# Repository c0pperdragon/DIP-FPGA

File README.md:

# DIP-FPGA
Breakout boards for FPGAs in DIP format.

## MachXO2 in a DIP 20
Assembled boards can be bought from
[my store at Tindie](https://www.tindie.com/stores/c0pperdragon/).

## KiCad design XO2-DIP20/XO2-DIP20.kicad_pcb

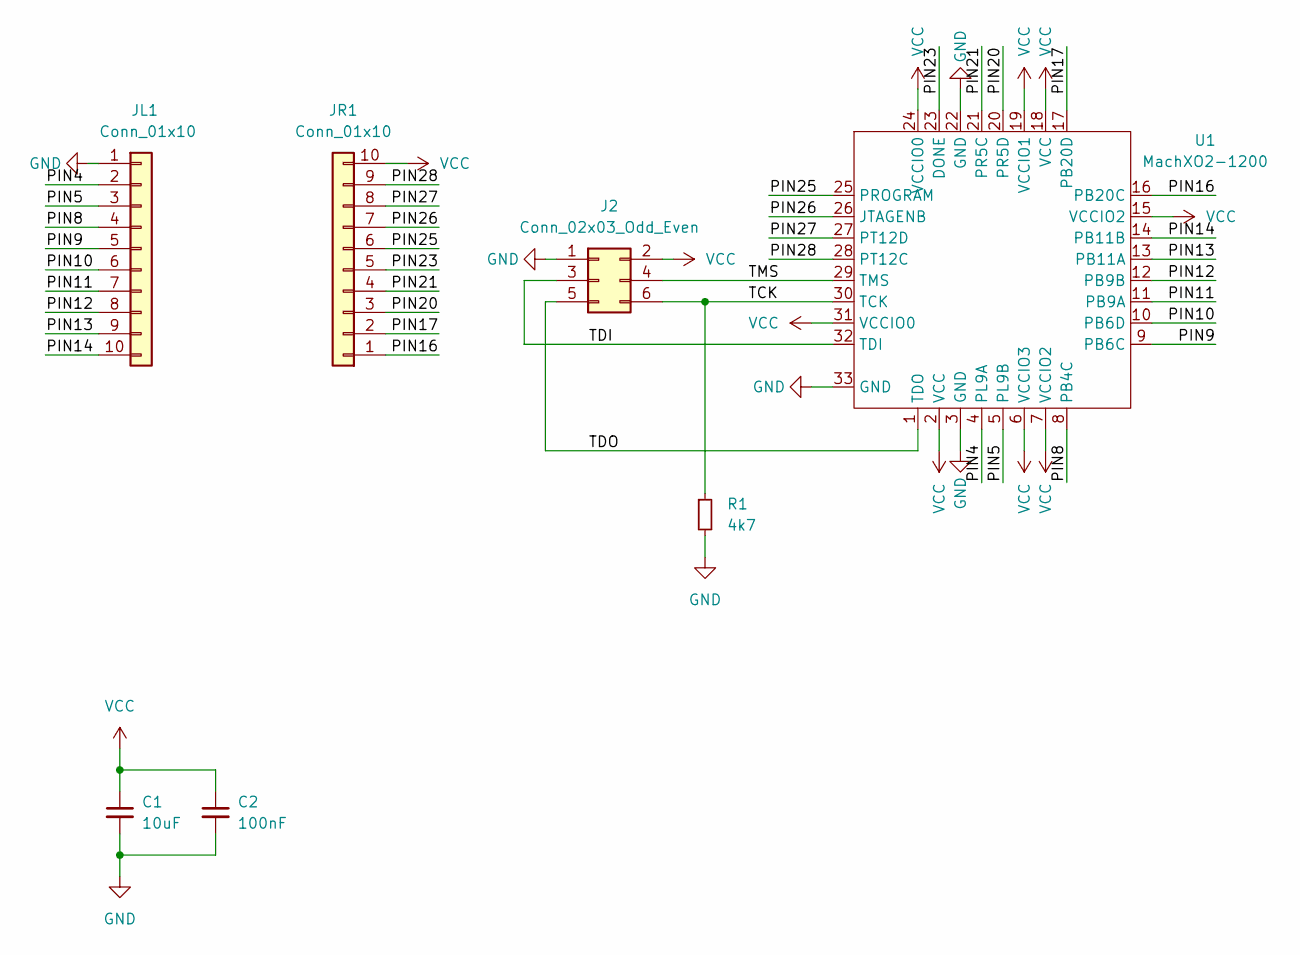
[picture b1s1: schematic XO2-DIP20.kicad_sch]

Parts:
C1: 10uF; C_0805_2012Metric_Pad1.18x1.45mm_HandSolder
C2: 100nF; C_0603_1608Metric_Pad1.08x0.95mm_HandSolder
J2: Conn_02x03_Odd_Even; PinHeader_2x03_P2.54mm_Vertical
JL1: Conn_01x10; PinHeader_1x10_P2.54mm_Vertical
JR1: Conn_01x10; PinHeader_1x10_P2.54mm_Vertical
R1: 4k7; R_0603_1608Metric_Pad0.98x0.95mm_HandSolder
U1: MachXO2-1200; QFN-32-1EP_5x5mm_P0.5mm_EP3.1x3.1mm_ThermalVias

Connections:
/PIN4: JL1.2, U1.4 (PL9A)
/PIN5: JL1.3, U1.5 (PL9B)
/PIN8: JL1.4, U1.8 (PB4C)
/PIN9: JL1.5, U1.9 (PB6C)
/PIN10: JL1.6, U1.10 (PB6D)
/PIN11: JL1.7, U1.11 (PB9A)
/PIN12: JL1.8, U1.12 (PB9B)
/PIN13: JL1.9, U1.13 (PB11A)
/PIN14: JL1.10, U1.14 (PB11B)
/PIN16: JR1.1, U1.16 (PB20C)
/PIN17: JR1.2, U1.17 (PB20D)
/PIN20: JR1.3, U1.20 (PR5D)
/PIN21: JR1.4, U1.21 (PR5C)
/PIN23: JR1.5, U1.23 (DONE)
/PIN25: JR1.6, U1.25 (PROGRAM)
/PIN26: JR1.7, U1.26 (JTAGENB)
/PIN27: JR1.8, U1.27 (PT12D)
/PIN28: JR1.9, U1.28 (PT12C)
/TCK: J2.6, R1.1, U1.30 (TCK)
/TDI: J2.3, U1.32 (TDI)
/TDO: J2.5, U1.1 (TDO)
/TMS: J2.4, U1.29 (TMS)
GND: C1.2, C2.2, J2.1, JL1.1, R1.2, U1.3 (GND), U1.22 (GND), U1.33 (GND)
VCC: C1.1, C2.1, J2.2, JR1.10, U1.2 (VCC), U1.6 (VCCIO3), U1.7 (VCCIO2), U1.15 (VCCIO2), U1.18 (VCC), U1.19 (VCCIO1), U1.24 (VCCIO0), U1.31 (VCCIO0)

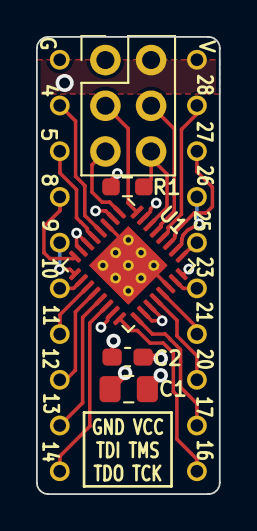
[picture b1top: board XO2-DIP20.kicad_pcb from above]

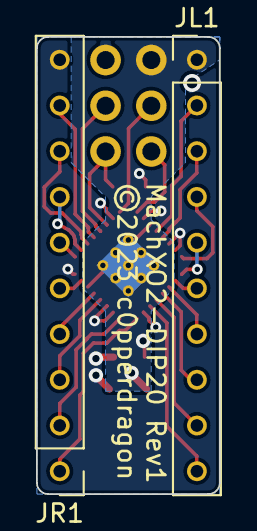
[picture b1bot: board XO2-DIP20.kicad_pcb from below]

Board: 2 copper layers, 10.2 x 25.4 mm, 7 parts (2 on the bottom side), 24 nets.

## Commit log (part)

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2023-05-24 Initial design
2023-05-24 Ignore backups
2023-05-25 Finish PCB design
2023-05-28 Prepare creating gerbers
2023-06-06 Example LED animation
2023-06-07 Picture of finished device
2023-06-10 Add link to store
2023-06-11 Reorganize examples
2023-06-15 Examples
2023-07-28 Use only one differential input for the example
2024-04-30 Implement test for clock glitch compensation
2024-06-24 PLL tolerance test
2024-09-05 Implement an ADC with a differential input
2025-11-07 More fun with video signal examples
2025-11-07 Various VGA test pictures (with sync-on-green)
2025-11-08 Investigate possibility to make a video PLL with 1ns jitter.
2025-11-08 Create output signal with finely grained timing.
2025-11-11 More experiments with the analog input circuitry
2025-11-13 Get CSYNC from dedicated input
2025-11-14 Increase accuracy by measuring 8 lines for total line time.
2025-11-14 Allow nanosecond-precision on setting the phase shift
2025-11-15 Generate some video to show input signal

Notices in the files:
XO2-DIP20/XO2-DIP20.kicad_pcb:
©2023 c0pperdragon
